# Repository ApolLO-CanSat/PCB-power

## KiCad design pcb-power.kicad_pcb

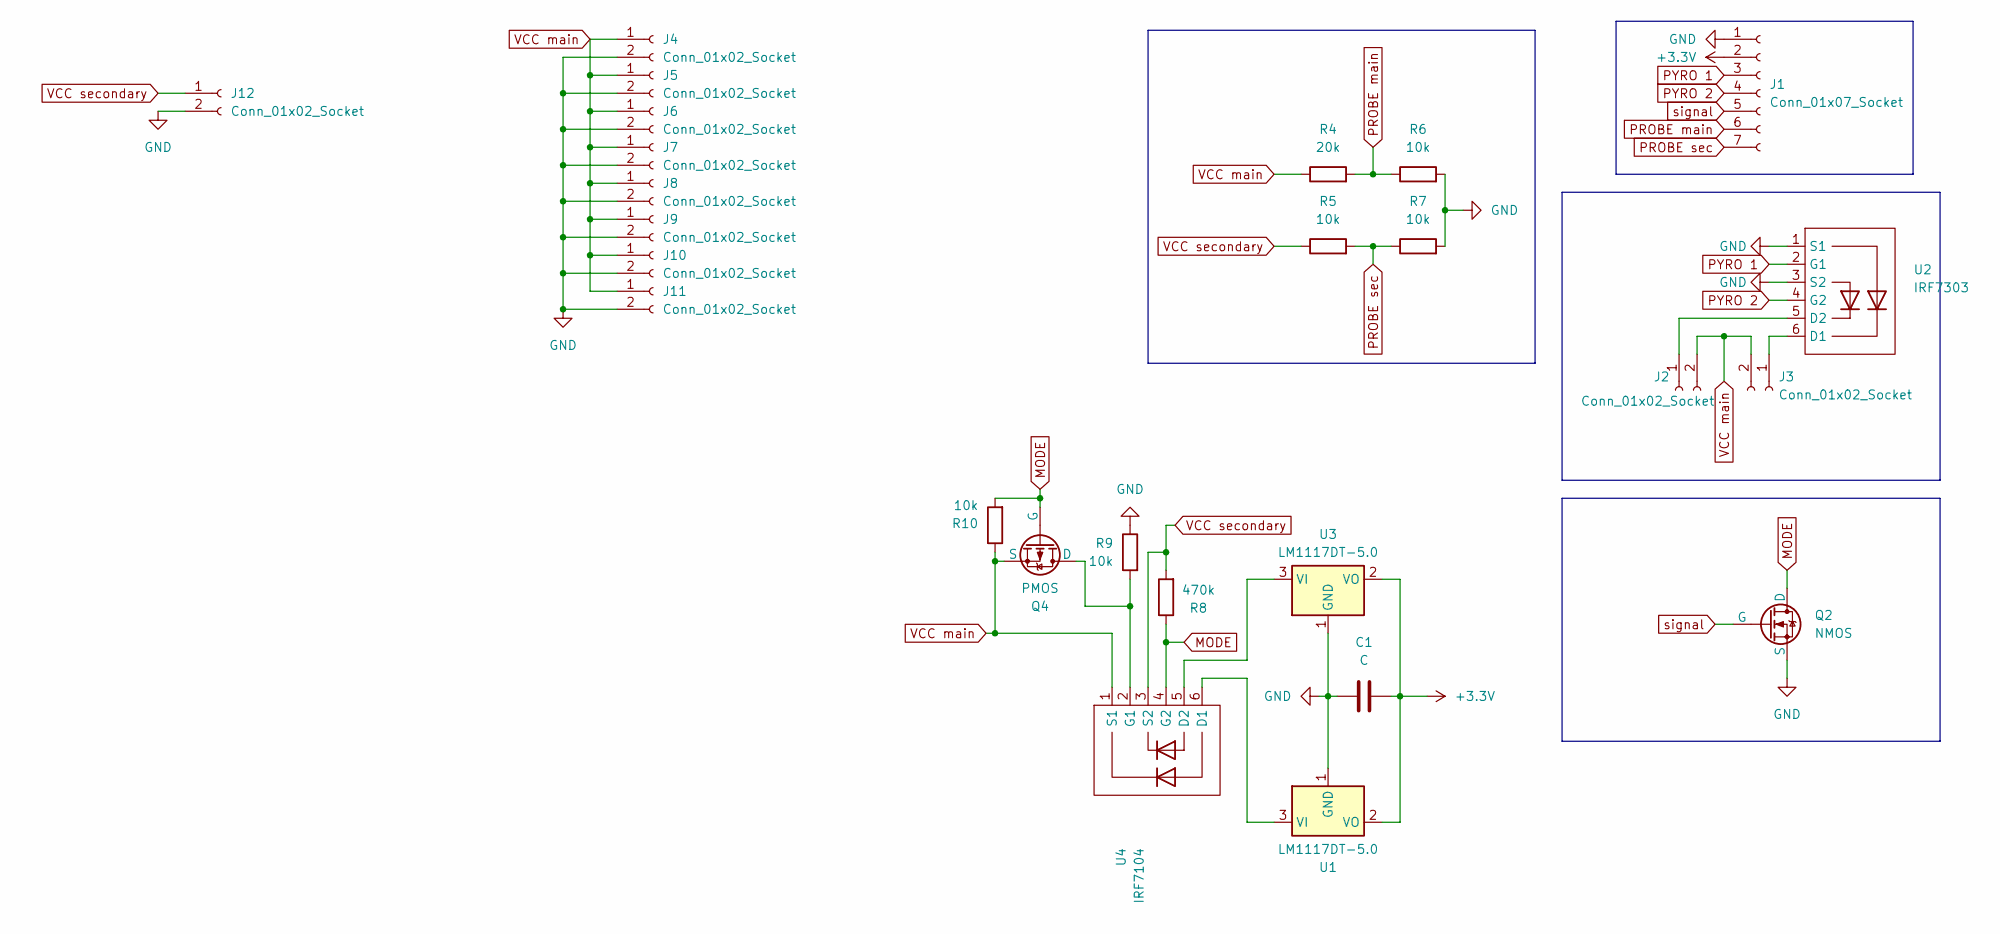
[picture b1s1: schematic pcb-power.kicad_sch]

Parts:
C1: C; CP_Radial_D5.0mm_P2.00mm
J1: Conn_01x07_Socket; PinSocket_1x07_P2.54mm_Vertical
J2, J3: Conn_01x02_Socket; TerminalBlock_bornier-2_P5.08mm
J4, J5, J6, J7, J8, J9, J10, J11, J12: Conn_01x02_Socket; PinSocket_1x02_P2.54mm_Vertical
Q2: NMOS; SOT-23
Q4: PMOS; TO-252-2
R4: 20k; R_Axial_DIN0207_L6.3mm_D2.5mm_P10.16mm_Horizontal
R5, R6, R7, R9, R10: 10k; R_Axial_DIN0207_L6.3mm_D2.5mm_P10.16mm_Horizontal
R8: 470k; R_Axial_DIN0207_L6.3mm_D2.5mm_P10.16mm_Horizontal
U1, U3: LM1117DT-5.0; TO-252-2
U2: IRF7303
U4: IRF7104

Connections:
+3.3V: C1.2, J1.2, U1.2 (VO), U3.2 (VO)
GND: C1.1, J1.1, J4.2, J5.2, J6.2, J7.2, J8.2, J9.2, J10.2, J11.2, J12.2, Q2.3 (S), R6.2, R7.2, R9.1, U1.1 (GND), U2.1 (S1), U2.3 (S2), U3.1 (GND)
MODE: Q2.1 (D), Q4.2 (G), R8.1, R10.2, U4.4 (G2)
unnamed: J2.1, U2.5 (D2)
unnamed: J3.1, U2.6 (D1)
unnamed: Q4.1 (D), R9.2, U4.2 (G1)
unnamed: U1.3 (VI), U4.6 (D1)
unnamed: U3.3 (VI), U4.5 (D2)
PROBE main: J1.6, R4.2, R6.1
PROBE sec: J1.7, R5.2, R7.1
PYRO 1: J1.3, U2.2 (G1)
PYRO 2: J1.4, U2.4 (G2)
VCC main: J2.2, J3.2, J4.1, J5.1, J6.1, J7.1, J8.1, J9.1, J10.1, J11.1, Q4.3 (S), R4.1, R10.1, U4.1 (S1)
VCC secondary: J12.1, R5.1, R8.2, U4.3 (S2)
signal: J1.5, Q2.2 (G)

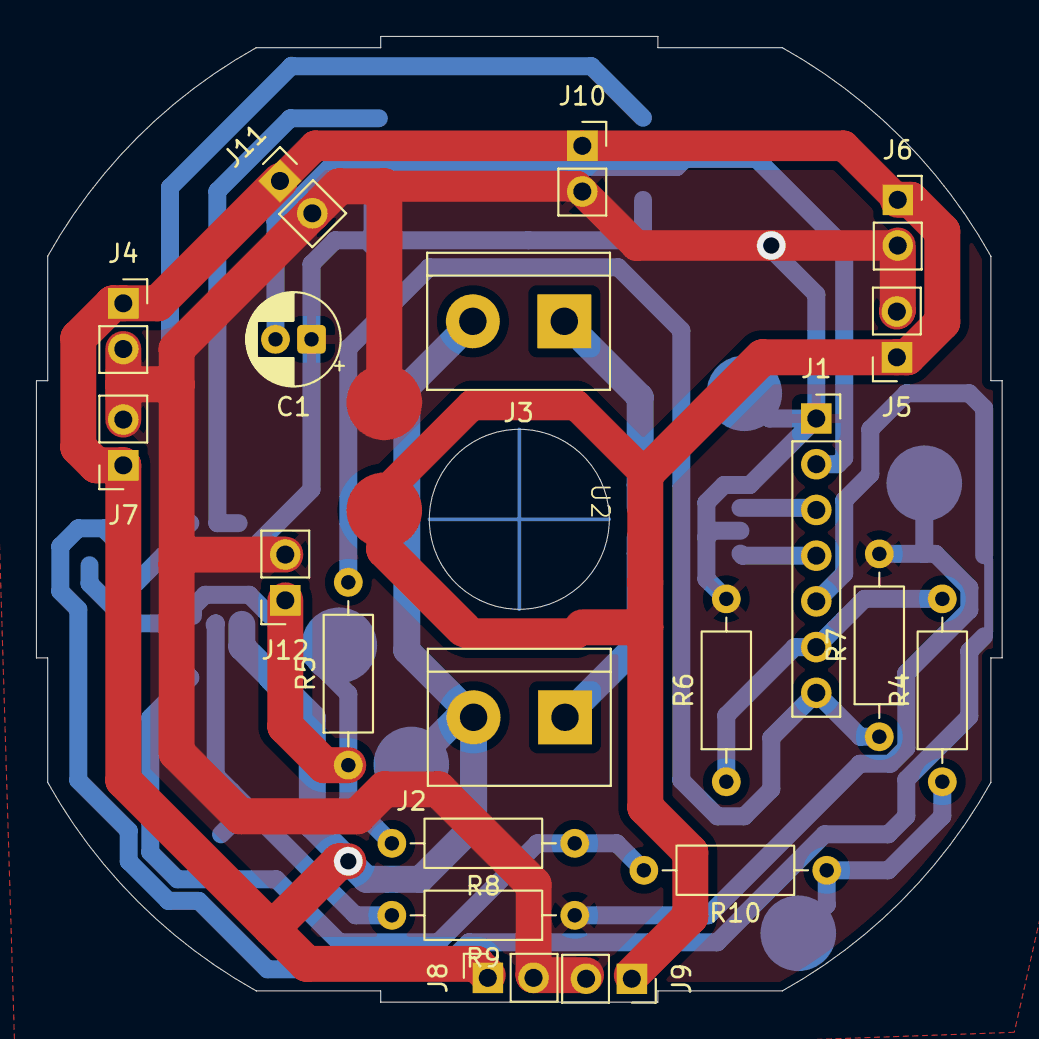
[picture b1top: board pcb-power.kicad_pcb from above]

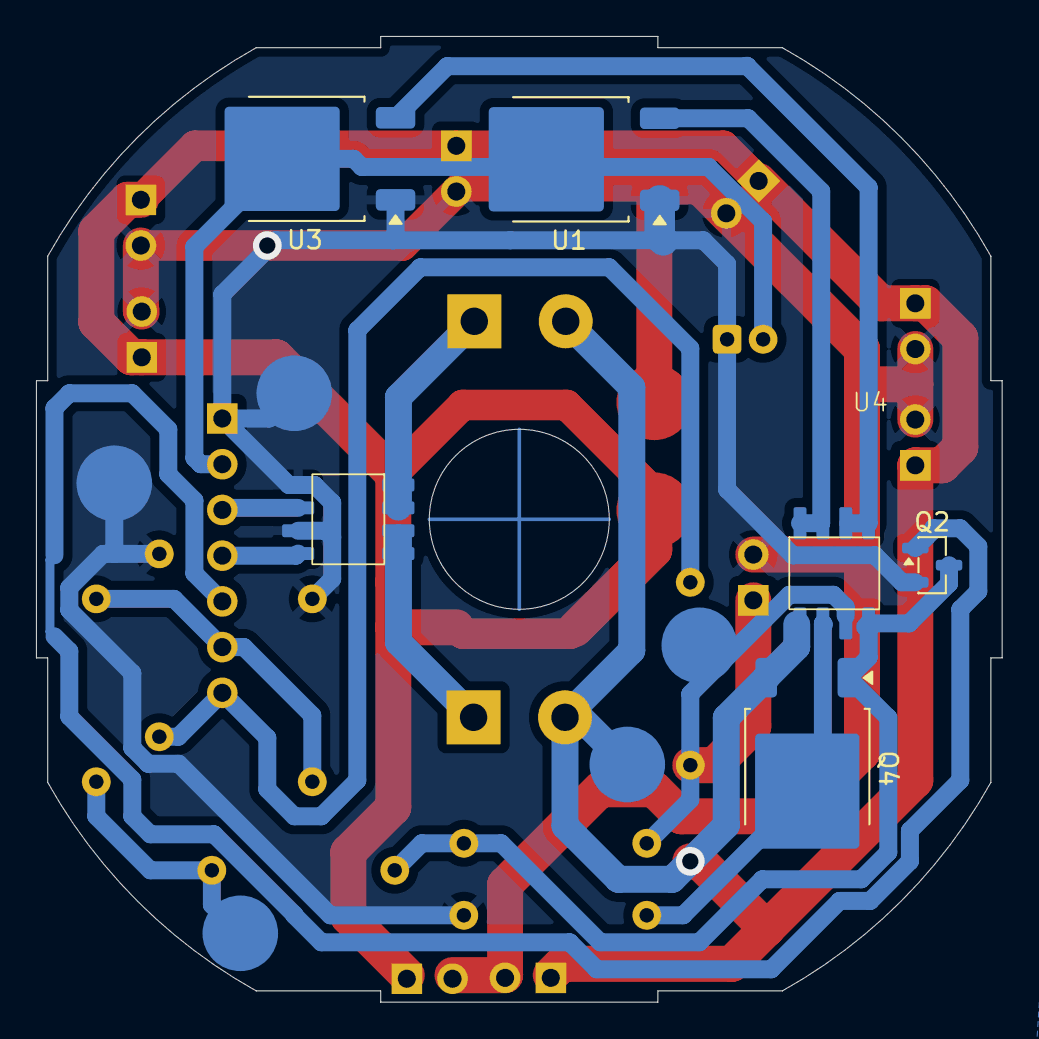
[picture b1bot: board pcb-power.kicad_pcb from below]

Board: 2 copper layers, 53.6 x 53.7 mm, 26 parts (6 on the bottom side), 15 nets.

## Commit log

2026-02-02 battery switches added
2026-02-12 added pyro, voltage probes, signal
2026-02-16 pcb design done
2026-02-18 added second layer for connecting batteries
2026-02-20 changed Vreg
2026-02-25 added GND via
2026-02-25 changed resistor value
